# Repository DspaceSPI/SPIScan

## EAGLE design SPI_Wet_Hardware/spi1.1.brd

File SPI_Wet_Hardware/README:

All this is from Paul - paul@taniwha.com

Wet end SPI board and software:

spi1.1.sch		- rev 1.1 eagle files
spi1.1.brd

gerbers/...		- what I taped out with

avr162write.cmd 	- shell script to init the serial USB chip
arduino-16usb/ 		- code it was inited with

main.cmd 		- shell script to init the main cpu
stk500boot_v2_mega2560.hex - code to init it with

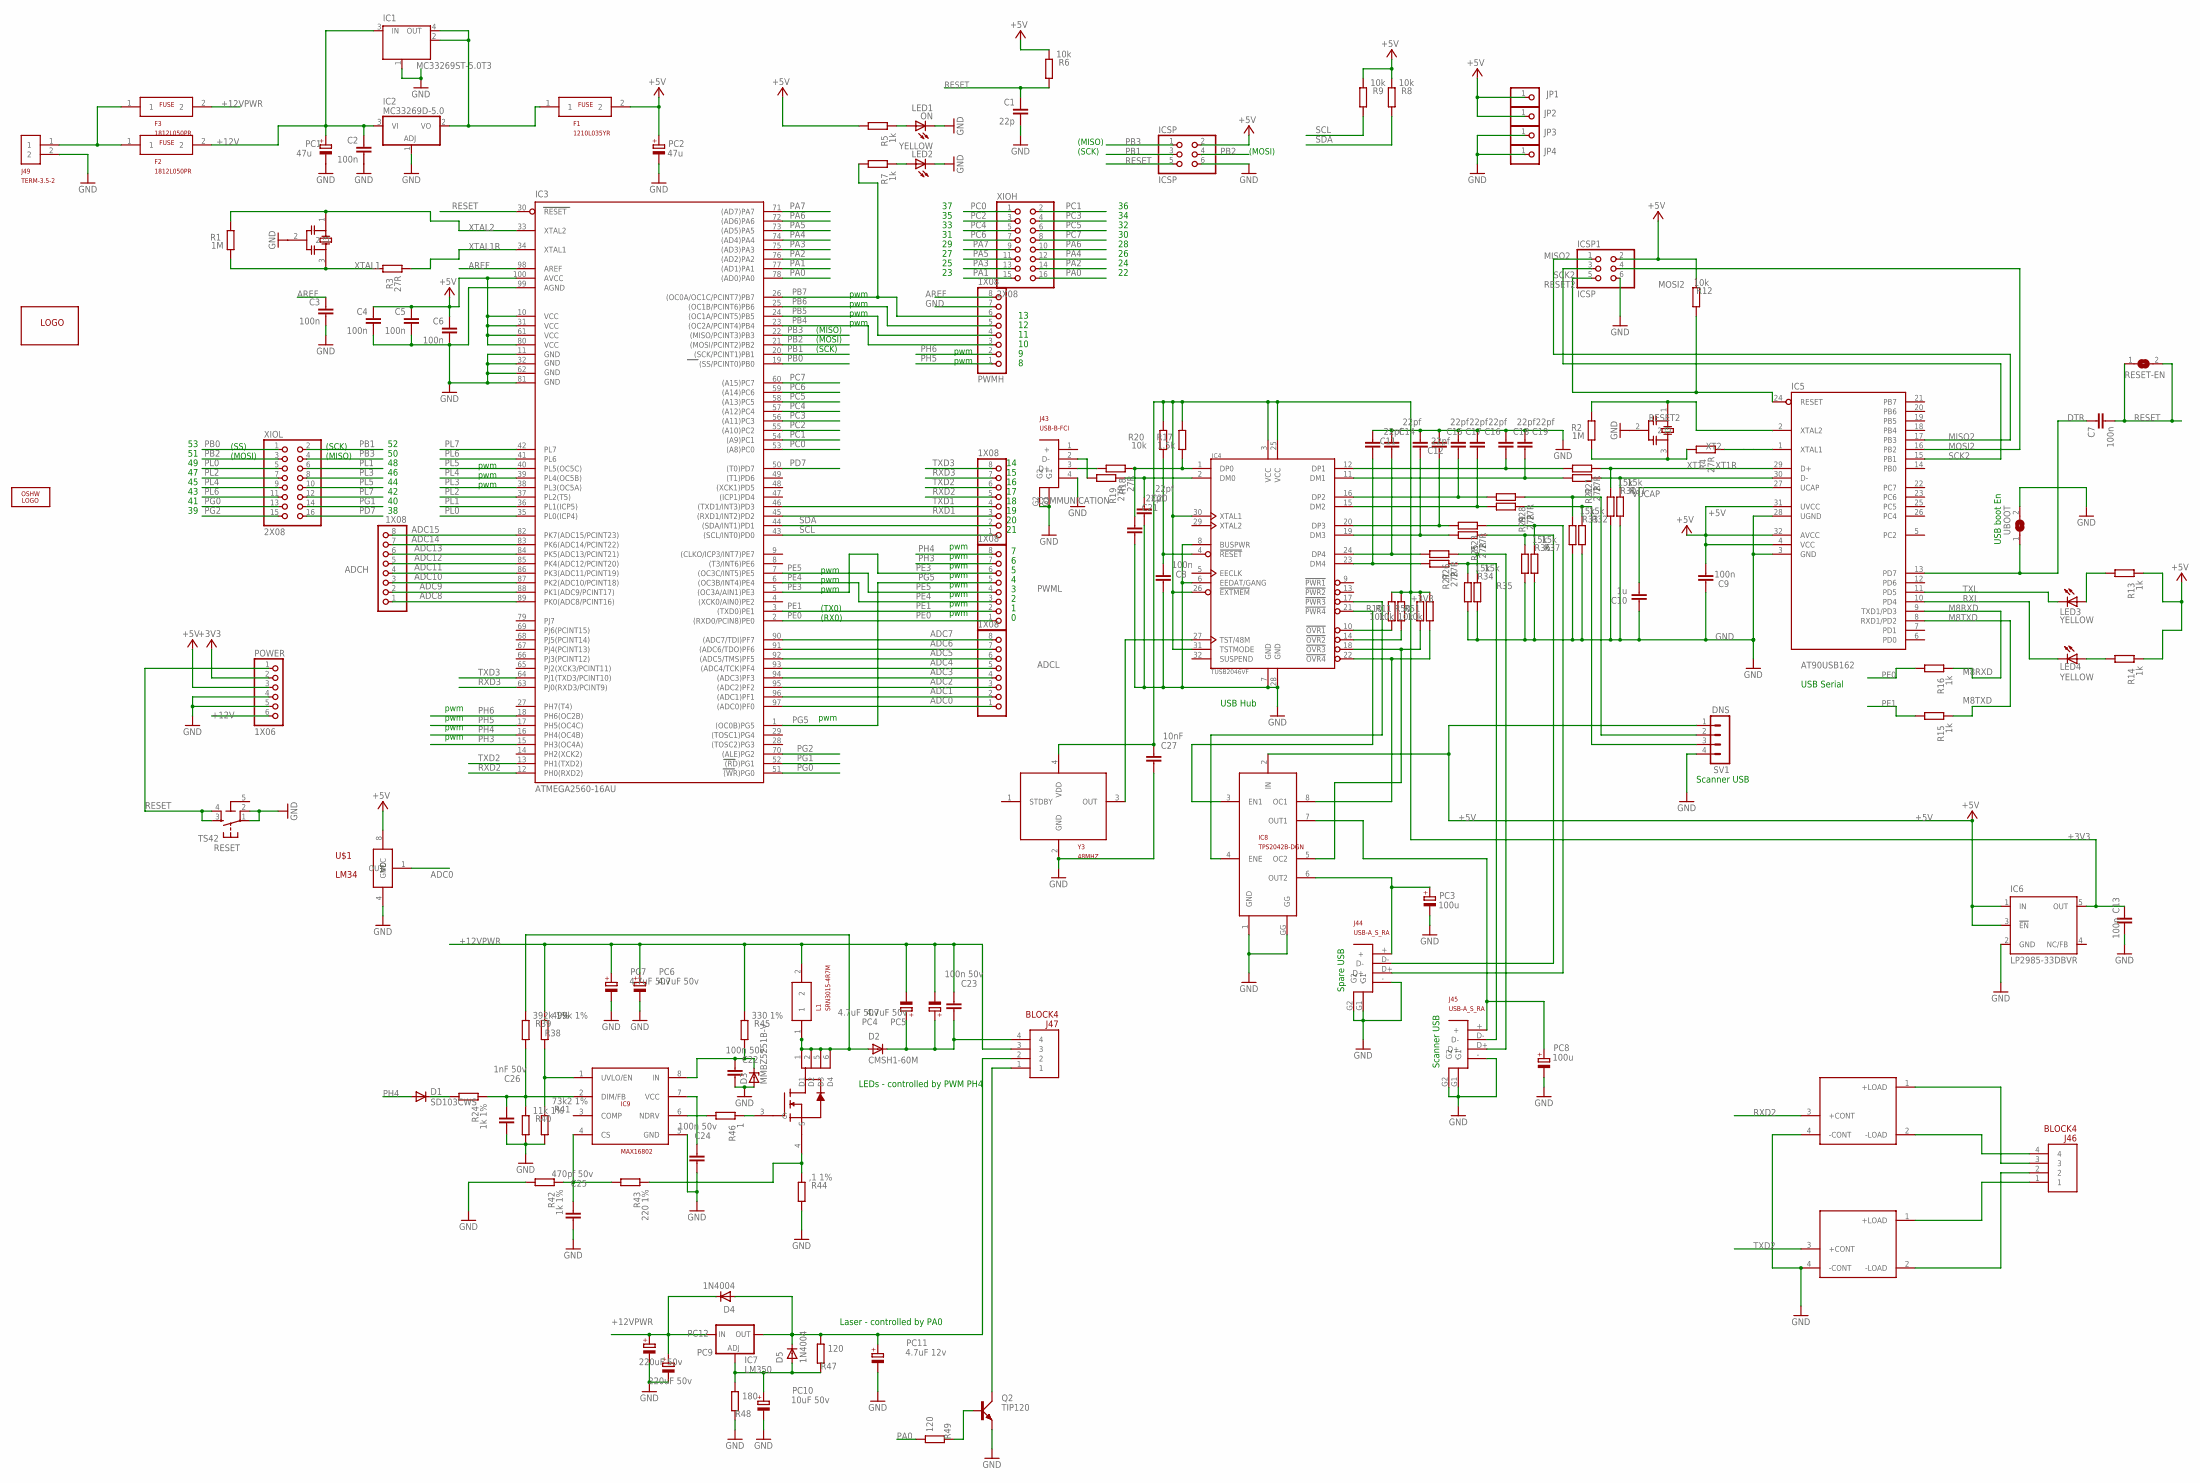
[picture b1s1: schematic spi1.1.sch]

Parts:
ADCH: 1X08
ADCL: 1X08
C1: 22p; C0603-ROUND
C2, C3, C4, C5, C6, C7, C8, C9, C13: 100n; C0603-ROUND
C10: 1u; C0603-ROUND
C11, C12, C14, C15, C16, C17, C18, C19, C20, C21: 22pf; C0603-ROUND
C22, C23, C24: 100n 50v; C0603-ROUND
C25: 470pf 50v; C0603-ROUND
C26: 1nF 50v; C0603-ROUND
C27: 10nF; C0603-ROUND
COMMUNICATION: 1X08
D1: SD103CWS; SOD323-W
D2: CMSH1-60M; SMA-DO214AC
D3: MMBZ5251B-V; SOT23
D4, D5: 1N4004; SMA-DO214AC
F1: 1210L035YR; POLY6
F2, F3: 1812L050PR; POLY15
IC1: MC33269ST-5.0T3; SOT223
IC2: MC33269D-5.0; DPACK
IC3: ATMEGA2560-16AU; TQFP100
IC4: TUSB2046VF; TQFP32-08
IC5: AT90USB162; TQFP32-08
IC6: LP2985-33DBVR; SOT23-DBV
IC7: LM350; 317TS
IC8: TPS2042B-DGN; DGN-8
IC9: MAX16802; USOP-8
ICSP, ICSP1: ICSP; 2X03
J43: USB-B-FCI; USB-B
J44, J45: USB-A_S_RA; USB-A
J46, J47: BLOCK4; TERM3.5-4
J49: TERM-3.5-2; TERM3.5-2
JP1, JP2, JP3, JP4: PINHD-1X1; 1X01
L1: SRN3015-4R7M; INDUCT1
LED2, LED3, LED4: YELLOW; CHIP-LED0805
LOGO2: OSHW_LOGO_FILLX0350-NT; OSHW_FILLX350_NOTEXT
ON: LED1; CHIP-LED0805
PC1, PC2: 47u; UD-6,3X7,7_NICHICON
PC3, PC8: 100u; UD-6,3X7,7_NICHICON
PC4, PC5, PC6, PC7: 4.7uF 50v; PANASONIC_C
PC9, PC12: 220uF 50v; PANASONIC_G
PC10: 10uF 50v; PANASONIC_D
PC11: 4.7uF 12v; PANASONIC_C
POWER: 1X06
PWMH: 1X08
PWML: 1X08
Q2: TIP120; TO220AV
R1, R2: 1M; R0603-ROUND
R3, R4, R18, R19, R21, R22, R23, R25, R26, R27, R28, R29: 27R; R0603-ROUND
R5, R7, R13, R14, R15, R16: 1k; R0603-ROUND
R6, R8, R9, R10, R11, R12, R20, R50, R51: 10k; R0603-ROUND
R17: 1.5k; R0603-ROUND
R24, R42: 1k 1%; R0603-ROUND
R30, R31, R32, R33, R34, R35, R36, R37: 15k; R0603-ROUND
R38: 499k 1%; R0603-ROUND
R39: 392k 1%; R0603-ROUND
R40: 11k 1%; R0603-ROUND
R41: 73k2 1%; R0603-ROUND
R43: 220 1%; R0603-ROUND
R44: ,1 1%; R1206
R45: 330 1%; R1206
R46: 1; R0603-ROUND
R47, R49: 120; R0603-ROUND
R48: 180; R0603-ROUND
RELAY1, RELAY2: XRELAY
RESET: TS42
RESET-EN: SJ
SV1: DNS; MA04-1
U$1: LM34; SS08
U$6: SI3458DVB; TSOP6
U$15: LOGO
UBOOT: SJ
XIOH: 2X08
XIOL: 2X08
Y1, Y2: AWSCR; RESONATOR1
Y3: 48MHZ; XTAL1

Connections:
5-GND: RESET.5 (5-GND)
+3V3: C13.2, C27.1, IC4.3 (VCC), IC4.25 (VCC), IC4.26 (!EXTMEM), IC4.30 (XTAL1), IC4.31 (TSTMODE), IC6.5 (OUT), POWER.2, R10.2, R11.2, R17.2, R20.2, R50.2, R51.2, Y3.4 (VDD)
+5V: C4.1, C5.1, C6.1, C9.1, F1.2, IC3.10 (VCC), IC3.31 (VCC1), IC3.61 (VCC2), IC3.80 (VCC3), IC3.100 (AVCC), IC5.4 (VCC), IC5.31 (UVCC), IC5.32 (AVCC), IC6.1 (IN), IC6.3 (!EN), IC8.2 (IN), ICSP.2, ICSP1.2, JP1.1, JP2.1, PC2.+, POWER.3, R5.2, R6.1, R8.1, R9.1, R12.1, R13.1, R14.1, SV1.1, U$1.8 (VCC)
+12V: C2.1, F2.2, IC1.3 (IN), IC2.3 (VI), PC1.+, POWER.6
+12VPWR: C23.1, D4.K (C), F3.2, IC7.3 (IN), J47.3, L1.2, PC4.-, PC5.-, PC6.+, PC7.+, PC9.+, PC12.+, R38.1, R45.1
ADC0: ADCL.1, IC3.97 ((ADC0)PF0), U$1.1 (OUT)
ADC1: ADCL.2, IC3.96 ((ADC1)PF1)
ADC2: ADCL.3, IC3.95 ((ADC2)PF2)
ADC3: ADCL.4, IC3.94 ((ADC3)PF3)
ADC4: ADCL.5, IC3.93 ((ADC4/TCK)PF4)
ADC5: ADCL.6, IC3.92 ((ADC5/TMS)PF5)
ADC6: ADCL.7, IC3.91 ((ADC6/TDO)PF6)
ADC7: ADCL.8, IC3.90 ((ADC7/TDI)PF7)
ADC8: ADCH.1, IC3.89 (PK0(ADC8/PCINT16))
ADC9: ADCH.2, IC3.88 (PK1(ADC9/PCINT17))
ADC10: ADCH.3, IC3.87 (PK2(ADC10/PCINT18))
ADC11: ADCH.4, IC3.86 (PK3(ADC11/PCINT19))
ADC12: ADCH.5, IC3.85 (PK4(ADC12/PCINT20))
ADC13: ADCH.6, IC3.84 (PK5(ADC13/PCINT21))
ADC14: ADCH.7, IC3.83 (PK6(ADC14/PCINT22))
ADC15: ADCH.8, IC3.82 (PK7(ADC15/PCINT23))
AREF: C3.1, IC3.98 (AREF), PWMH.8
DTR: C7.1, IC5.13 (PD7), UBOOT.1
GND: C1.2, C2.2, C3.2, C4.2, C5.2, C6.2, C8.2, C9.2, C10.2, C11.1, C12.1, C13.1, C14.1, C15.1, C16.1, C17.1, C18.1, C19.1, C20.2, C21.2, C22.2, C24.2, C25.2, C26.2, C27.2, D3.1 (A), IC1.1 (GND/ADJ), IC2.1 (ADJ), IC3.11 (GND), IC3.32 (GND1), IC3.62 (GND2), IC3.81 (GND3), IC3.99 (AGND), IC4.6 (EEDAT/GANG), IC4.7 (GND), IC4.8 (BUSPWR), IC4.28 (GND), IC5.3 (GND), IC5.28 (UGND), IC6.2 (GND), IC8.1 (GND), IC8.GG, IC9.5 (GND), ICSP.6, ICSP1.6, J43.4 (-), J43.G1, J43.G2, J44.-, J44.G1, J44.G2, J45.-, J45.G1, J45.G2, J49.2, JP3.1, JP4.1, LED2.C, ON.C, PC1.-, PC2.-, PC3.-, PC6.-, PC7.-, PC8.-, PC9.-, PC10.-, PC11.-, PC12.-, POWER.4, POWER.5, PWMH.7, Q2.E, R30.2, R31.2, R32.2, R33.2, R34.2, R35.2, R36.2, R37.2, R40.2, R41.2, R42.2, R44.2, R48.2, RELAY1.4 (-CONT), RELAY2.4 (-CONT), RESET.1, RESET.2, SV1.4, U$1.4 (GND), UBOOT.2, Y1.2, Y2.2, Y3.2 (GND)
M8RXD: IC5.9 (TXD1/PD3), R16.1
M8TXD: IC5.8 (RXD1/PD2), R15.1
MISO2: IC5.17 (PB3), ICSP1.1
MOSI2: IC5.16 (PB2), ICSP1.4
unnamed: J44.D+, R23.1, R37.1
unnamed: LED2.A, R7.1
unnamed: ON.A, R5.1
unnamed: R28.1, R33.1, SV1.2
unnamed: R29.1, R32.1, SV1.3
unnamed: IC4.10 (!OVR1), R10.1
unnamed: IC4.14 (!OVR2), R11.1
unnamed: IC4.17 (!PWR3), IC8.4 (ENE)
unnamed: C21.1, IC4.1 (DP0), R17.1, R18.1
unnamed: J45.D+, R26.1, R35.1
unnamed: C8.1, IC4.4 (!RESET), R20.1
unnamed: IC4.21 (!PWR4), IC8.3 (EN1)
unnamed: IC4.18 (!OVR3), IC8.5 (OC2), R50.1
unnamed: IC4.22 (!OVR4), IC8.8 (OC1), R51.1
unnamed: IC8.6 (OUT2), J44.+, PC3.+
unnamed: IC8.7 (OUT1), J45.+, PC8.+
unnamed: C15.2, IC4.20 (DP3), R23.2
unnamed: C17.2, IC4.16 (DP2), R28.2
unnamed: C16.2, IC4.15 (DM2), R29.2
unnamed: C12.2, IC4.19 (DM3), R25.2
unnamed: C14.2, IC4.24 (DP4), R26.2
unnamed: C11.2, IC4.23 (DM4), R27.2
unnamed: C18.2, IC4.12 (DP1), R21.2
unnamed: C19.2, IC4.11 (DM1), R22.2
unnamed: IC5.30 (D-), R22.1, R31.1
unnamed: IC5.29 (D+), R21.1, R30.1
unnamed: C20.1, IC4.2 (DM0), R19.1
unnamed: J44.D-, R25.1, R36.1
unnamed: D1.C, R24.2
unnamed: C26.1, IC9.2 (DIM/FB), R24.1, R39.2, R40.1
unnamed: J45.D-, R27.1, R34.1
unnamed: IC9.1 (UVLO/EN), R38.2, R41.1
unnamed: C23.2, D2.K (C), J47.4, PC4.+, PC5.+
unnamed: IC4.27 (TST/48M), Y3.3 (OUT)
unnamed: D2.A, L1.1, R39.1, U$6.1 (D1), U$6.2 (D2), U$6.5 (D3), U$6.6 (D4)
unnamed: C24.1, IC9.7 (VCC)
unnamed: F1.1, IC1.2 (OUT), IC1.4 (OUT), IC2.2 (VO)
unnamed: C25.1, IC9.4 (CS), R42.1, R43.2
unnamed: D5.A, IC7.1 (ADJ), PC10.+, R47.2, R48.1
unnamed: C22.1, D3.3 (C), IC9.8 (IN), R45.2
unnamed: R43.1, R44.1, U$6.4 (S)
unnamed: F2.1, F3.1, J49.1
unnamed: IC9.6 (NDRV), R46.2
unnamed: R46.1, U$6.3 (G)
unnamed: J43.2 (D-), R19.2
unnamed: J43.3 (D+), R18.2
unnamed: D4.A, D5.K (C), IC7.2 (OUT), J47.2, PC11.+, R47.1
unnamed: J47.1, Q2.C
unnamed: J46.4, RELAY1.2 (-LOAD)
unnamed: J46.1, RELAY2.1 (+LOAD)
unnamed: J46.3, RELAY1.1 (+LOAD)
unnamed: Q2.B, R49.2
unnamed: J46.2, RELAY2.2 (-LOAD)
unnamed: LED4.A, R14.2
unnamed: LED3.A, R13.2
PA0: IC3.78 ((AD0)PA0), R49.1, XIOH.16
PA1: IC3.77 ((AD1)PA1), XIOH.15
PA2: IC3.76 ((AD2)PA2), XIOH.14
PA3: IC3.75 ((AD3)PA3), XIOH.13
PA4: IC3.74 ((AD4)PA4), XIOH.12
PA5: IC3.73 ((AD5)PA5), XIOH.11
PA6: IC3.72 ((AD6)PA6), XIOH.10
PA7: IC3.71 ((AD7)PA7), XIOH.9
PB0: IC3.19 ((SS/PCINT0)PB0), XIOL.1
PB1: IC3.20 ((SCK/PCINT1)PB1), ICSP.3, XIOL.2
PB2: IC3.21 ((MOSI/PCINT2)PB2), ICSP.4, XIOL.3
PB3: IC3.22 ((MISO/PCINT3)PB3), ICSP.1, XIOL.4
PB4: IC3.23 ((OC2A/PCINT4)PB4), PWMH.3
PB5: IC3.24 ((OC1A/PCINT5)PB5), PWMH.4
PB6: IC3.25 ((OC1B/PCINT6)PB6), PWMH.5
PB7: IC3.26 ((OC0A/OC1C/PCINT7)PB7), PWMH.6, R7.2
PC0: IC3.53 ((A8)PC0), XIOH.1
PC1: IC3.54 ((A9)PC1), XIOH.2
PC2: IC3.55 ((A10)PC2), XIOH.3
PC3: IC3.56 ((A11)PC3), XIOH.4
PC4: IC3.57 ((A12)PC4), XIOH.5
PC5: IC3.58 ((A13)PC5), XIOH.6
PC6: IC3.59 ((A14)PC6), XIOH.7
PC7: IC3.60 ((A15)PC7), XIOH.8
PD7: IC3.50 ((T0)PD7), XIOL.16
PE0: IC3.2 ((RXD0/PCIN8)PE0), PWML.1, R16.2
PE1: IC3.3 ((TXD0)PE1), PWML.2, R15.2
PE3: IC3.5 ((OC3A/AIN1)PE3), PWML.6
PE4: IC3.6 ((OC3B/INT4)PE4), PWML.3
PE5: IC3.7 ((OC3C/INT5)PE5), PWML.4
PG0: IC3.51 ((WR)PG0), XIOL.13
PG1: IC3.52 ((RD)PG1), XIOL.14
PG2: IC3.70 ((ALE)PG2), XIOL.15
PG5: IC3.1 ((OC0B)PG5), PWML.5
PH3: IC3.15 (PH3(OC4A)), PWML.7
PH4: D1.A, IC3.16 (PH4(OC4B)), PWML.8
PH5: IC3.17 (PH5(OC4C)), PWMH.1
PH6: IC3.18 (PH6(OC2B)), PWMH.2
PL0: IC3.35 (PL0(ICP4)), XIOL.5
PL1: IC3.36 (PL1(ICP5)), XIOL.6
PL2: IC3.37 (PL2(T5)), XIOL.7
PL3: IC3.38 (PL3(OC5A)), XIOL.8
PL4: IC3.39 (PL4(OC5B)), XIOL.9
PL5: IC3.40 (PL5(OC5C)), XIOL.10
PL6: IC3.41 (PL6), XIOL.11
PL7: IC3.42 (PL7), XIOL.12
RESET: C1.1, C7.2, IC3.30 (RESET), ICSP.5, POWER.1, R6.2, RESET.3, RESET.4, RESET-EN.1, RESET-EN.2
RESET2: IC5.24 (RESET), ICSP1.5, R12.2
RXD1: COMMUNICATION.3, IC3.45 ((RXD1/INT2)PD2)
RXD2: COMMUNICATION.5, IC3.12 (PH0(RXD2)), RELAY1.3 (+CONT)
RXD3: COMMUNICATION.7, IC3.63 (PJ0(RXD3/PCINT9))
RXL: IC5.10 (PD4), LED4.C
SCK2: IC5.15 (PB1), ICSP1.3
SCL: COMMUNICATION.1, IC3.43 ((SCL/INT0)PD0), R9.2
SDA: COMMUNICATION.2, IC3.44 ((SDA/INT1)PD1), R8.2
TXD1: COMMUNICATION.4, IC3.46 ((TXD1/INT3)PD3)
TXD2: COMMUNICATION.6, IC3.13 (PH1(TXD2)), RELAY2.3 (+CONT)
TXD3: COMMUNICATION.8, IC3.64 (PJ1(TXD3/PCINT10))
TXL: IC5.11 (PD5), LED3.C
VUCAP: C10.1, IC5.27 (UCAP)
XT1: R2.1, R4.2, Y2.3
XT1R: IC5.1 (XTAL1), R4.1
XT2: IC5.2 (XTAL2), R2.2, Y2.1
XTAL1: R1.1, R3.2, Y1.3
XTAL1R: IC3.34 (XTAL1), R3.1
XTAL2: IC3.33 (XTAL2), R1.2, Y1.1

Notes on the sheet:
(SCK)
(MISO)
(MOSI)
pwm
(TX0)
(RX0)
(SS)
USB boot En
Scanner USB
USB Serial
USB Hub
Spare USB
Laser - controlled by PA0
LEDs - controlled by PWM PH4

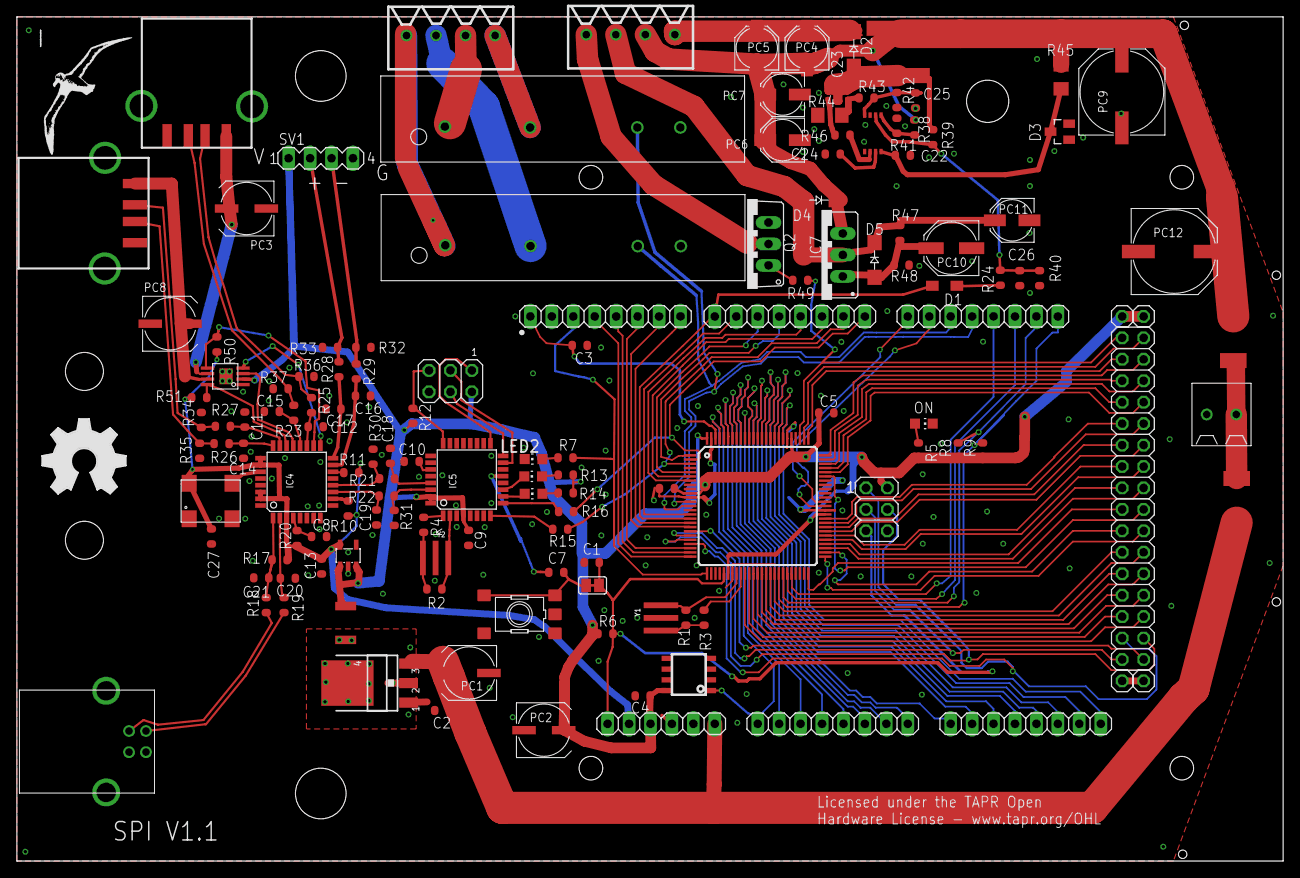
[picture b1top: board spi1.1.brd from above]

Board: 2 copper layers, 150.0 x 100.0 mm, 146 parts (1 on the bottom side), 148 nets.

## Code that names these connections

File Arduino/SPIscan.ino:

/*
Process serial commands from the host and send responses
Serial packet protocol is:
 <sync>       Byte, always 0xAA
 <command>    Byte
 <transID>    Byte
 <paramLen>   Byte
 <parameters> Byte array, paramLen bytes (could be 0)
 <checksum>   Byte, low byte of sum of <sync>..<last parameter>
 
<transID> is sent by the host and used in any response(s) and can be any value
except 00, which is reserved for messages sent by the Arduino without being asked.

The Arduino is predefined as driving:
 - two pump relays on RXD2 and TXD2
 - a PWM LED drive PH4
 - a laser enable PA0
 - a temp sensor on PC7 (A15)
 
*/

#include "SPIproto.h"      // Serial protocol constants

// Configurable parameters
enum {
  kBaudRate = 115200,
  kMaxMsgSize = 50,      // Max data size
  
  kTotalSize = kHdrSize + kMaxMsgSize + kCksumSize,
};

// Less configurable parameters
const char kSysInfoStr[] = "SPIScan " __DATE__ __TIME__ ;

//====================== Predefined pins  ======================

enum {
  kOnboardLEDPin = 13,
  kPump1Pin = 16,
  kPump2Pin = 17
  
};

struct KnownPin {
  byte pinNum;
  bool outDir;
  bool outState;
};

const KnownPin gPredefinedPins[] = {
  { kOnboardLEDPin, OUTPUT, LOW },    // Onboard LED
  { kPump1Pin, OUTPUT, LOW },    // PH0(RXD2) pump drive
  { kPump2Pin, OUTPUT, LOW },    // PH1(TXD2) pump drive
  { 7,  OUTPUT, LOW },    // PH4 LED drive (PWM)
  { 22, OUTPUT, LOW }     // PA0 laser enable
};

enum { kNPredefs = sizeof(gPredefinedPins)/sizeof(KnownPin) };

//======================= Globals ========================
byte   gInMsg[kTotalSize];
byte   gCkSum = 0;
Sp_Error   gNetErr = kNoErr;      // Last error 
long   gNetParam;    // Last error parameter
short  gInWrIdx = 0;

// ----------------------- Packet protocol --------------------------

void SendMsg(Sp_Command cmd, byte transID, const void* p, byte len)
{
  int i;
  byte header[kHdrSize] = { kSyncByte, cmd, transID, len };
  byte cksum = kSyncByte + cmd + transID + len;
  
  Serial.write(&header[0],kHdrSize);
  if (len>0) {
     const byte* bp = (byte*)p;
     for (i=0; i<len; i++)
        cksum += bp[i];
     Serial.write(bp,len);
  }
  Serial.write(cksum);
}

void SendErrMsg(Sp_Error errcode, byte transID, long parameter)
{
  uint8_t msg[5] = { errcode, parameter>>24, parameter>>16, parameter>>8, parameter & 0xFF };
  SendMsg(kCCError, transID, &msg, sizeof(msg));
}

void SendMsgOrNetErr(Sp_Command resp, byte transID, void* dataP, byte nBytes)
// Either send specified message or an error code if gNetErr is nonzero: useful
// for responding to list messages
{
  if (gNetErr==kNoErr)
    SendMsg(resp,transID,dataP,nBytes);
  else
    SendErrMsg(gNetErr,transID,gNetParam);
}

bool GetMsg()
// Call whenever convenient, will return true if a valid and complete message is in the gInMsg buffer
// If it returns true you *must* process the message before calling again
{
   int i,n;
   byte b;
   
   n = Serial.available();
   
   for (i=0; i<n; i++) {
     b = Serial.read();
     //Serial.write(b);
     if (gInWrIdx==0) {
       if (b==kSyncByte) {
         gInMsg[gInWrIdx++] = b;
         gCkSum = b;
       }
     } else {
        if (gInWrIdx < kTotalSize)
          gInMsg[gInWrIdx++] = b;
        if (gInWrIdx > kLenPos && gInWrIdx >= kHdrSize + gInMsg[kLenPos] + kCksumSize) {
            // Message complete; reset wridx
            gInWrIdx = 0;
            if (gCkSum != b) {
               return false;      // Ignore if it has a bad checksum
            } else if (gInMsg[kLenPos]>kMaxMsgSize) {
                SendErrMsg(kErrMsgOversize,gInMsg[kIDPos],gInMsg[kLenPos]);    // valid, but too big for buffer
                return false;
            } else
                return true; 
        } else
           gCkSum += b;
     }
   } // for
   return false;
}

//------------------------ Utilities ---------------------------------------

bool isInput(byte pinNum)
{
  volatile byte* rp = portModeRegister(digitalPinToPort(pinNum));
  return (*rp & digitalPinToBitMask(pinNum)) == 0;
}

bool isPredefined(byte aPin)
{
  int i;
  for (i=0 ; i<kNPredefs; i++) 
     if (gPredefinedPins[i].pinNum==aPin)
       return true;
  return false;
}

//------------------------ Core commands ----------------------------------

void SetMode(byte pinNum, byte value)
{
   // Check its a valid pin number and it doesn't have a predefined direction
   if (digitalPinToPort(pinNum)==NOT_A_PIN) {
      gNetErr = kErrInvalidPin;
      gNetParam = pinNum;
   } else if (isPredefined(pinNum)) {
      gNetErr = kErrPredefined;
      gNetParam = pinNum;
   } else
      pinMode(pinNum,value);
}

void SetPin(byte pinNum, byte value)
{
   // Check its a valid pin number and it isn't an input
   if (digitalPinToPort(pinNum)==NOT_A_PIN) {
      gNetErr = kErrInvalidPin;
      gNetParam = pinNum;
   } else if (isInput(pinNum)) {
      gNetErr = kErrOutToInput;
      gNetParam = pinNum;
   } else
      digitalWrite(pinNum,value);
}

byte GetPin(byte pinNum)
{
  // Check its a valid pin number. Its OK to read back from outputs
  if (digitalPinToPort(pinNum)==NOT_A_PIN) {
      gNetErr = kErrInvalidPin;
      gNetParam = pinNum;
      return LOW;
  } else 
      return digitalRead(pinNum);
}

void AnalogReadPinList(byte transID, byte* pinNums, byte nPins)
{
  int i;
  int gValues[kMaxMsgSize/sizeof(int)];
  
  for (i=0; i<nPins; i++)
    // Check for valid analog pin
    if (pinNums[i] > NUM_ANALOG_INPUTS) {
      gNetErr = kErrInvalidPin;
      gNetParam = pinNums[i];
    } else { 
      gValues[i] = analogRead(pinNums[i]);
    }
      
  SendMsgOrNetErr(kCCPinValues, transID, gValues, nPins);
}

void GetPinList(byte transID, byte* pinNums, byte nPins)
{
  int i;
  byte gValues[kMaxMsgSize];
  
  for (i=0; i<nPins; i++)
    gValues[i] = GetPin(pinNums[i]);
  SendMsgOrNetErr(kCCPinStates, transID, gValues, nPins);
}

void SetPinList(byte transID, byte* pinNums, byte nPins)
{
  int i;
  
  for (i=0; i<nPins; i++)
    SetPin(pinNums[i] & 0x7F, (pinNums[i] & 0x80) ? HIGH : LOW);
  SendMsgOrNetErr(kCCNoErr, transID, NULL, 0);
}

void SetModeList(byte transID, byte* pinNums, byte nPins)
{
  int i;
  
  for (i=0; i<nPins; i++)
    SetMode(pinNums[i] & 0x7F, (pinNums[i] & 0x80) ? OUTPUT : INPUT);
  SendMsgOrNetErr(kCCNoErr, transID, NULL, 0);
}

void AnalogWriteList(byte transID, byte* pvList, byte nValues)
{
  int i;
  byte pinNum;
  
  for (i=0; i<nValues; i++) {
    pinNum = pvList[0];
    if (isInput(pinNum)) {
      gNetErr = kErrOutToInput;
      gNetParam = pinNum;
    } else 
      analogWrite(pinNum, pvList[1]);
    pvList += 2;
  }
  SendMsgOrNetErr(kCCNoErr, transID, NULL, 0);
}

void ProcessMsg()
{
  gNetErr = kNoErr;
  switch (gInMsg[kCmdPos]) {
    
    case kCCGetPins:
      GetPinList(gInMsg[kIDPos], &gInMsg[kDataPos], gInMsg[kLenPos]);
      break;
      
    case kCCSetPins:
      SetPinList(gInMsg[kIDPos], &gInMsg[kDataPos], gInMsg[kLenPos]);
      break;
      
    case kCCSetPinModes:
      SetModeList(gInMsg[kIDPos], &gInMsg[kDataPos], gInMsg[kLenPos]);
      break;
    
    case kCCAnalogReads:
      AnalogReadPinList(gInMsg[kIDPos], &gInMsg[kDataPos], gInMsg[kLenPos]);
      break;
    
    case kCCSetPWM:
      if (gInMsg[kLenPos] & 1)    // Must be a list of pin/value pairs
        SendErrMsg(kErrOddPWM,gInMsg[kIDPos],gInMsg[kLenPos]);
      else
        AnalogWriteList(gInMsg[kIDPos], &gInMsg[kDataPos], gInMsg[kLenPos]/2);
      break;
    
    case kCCGetSysInfo: {
         SendMsg(kCCSysInfo,gInMsg[kIDPos],kSysInfoStr,strlen(kSysInfoStr));
      } break;
    
    default:
      SendErrMsg(kErrUnknownCmd, gInMsg[kIDPos], gInMsg[kCmdPos]);
      break;
  }
}


//---------------------------- Arduino main ------------------------

void setup()
{
   int i;
   
   // Setup predefined state
   for (i=0 ; i<kNPredefs; i++) {
     pinMode(gPredefinedPins[i].pinNum, gPredefinedPins[i].outDir);
     digitalWrite(gPredefinedPins[i].pinNum, gPredefinedPins[i].outState);
   }
   // Turn on serial port
   gInWrIdx = 0;
   Serial.begin(kBaudRate);
  
   SendMsg(kCCSysInfo,0,kSysInfoStr,strlen(kSysInfoStr));
}

long count = 0;

void loop()
{
   while (GetMsg())
     ProcessMsg();
}

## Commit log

2012-04-24 first drafts
2012-04-27 Added LiDE700F USB packet log for restart, preview, colour scan, and greyscale scan
2012-04-27 Added SANE Man Pages
2012-04-30 Added base structure for boat box electronics
2012-05-12 Seperate out protocol header, add typedefs for errors and command constants
2012-05-21 Added first DRAFT of SANE backend for Lide700f for intial test purposes
2012-06-09 Fix minor bugs, add demo host interface files in C/POSIX
2012-07-12 added wet end design and code
2012-07-12 remove .o files
2012-08-13 add file for Brian
2012-08-20 Add ability to initialise PWM outputs for LED at startup
2012-08-21 Added scanner control code (needs sane libraries to be installed) Added code to build python bindings for scanning and for Michael's Arduino RPC interface glue
2012-08-22 - added GPS code - changed arduino code to possibly handle usb being unplugged (untested) - created unified startup_dspace() that starts all these subsystems (should be called first by python)
2012-08-22 - push actual changes - gps changes - unified startup routines - try to add USB retry code to arduino code
2012-08-22 add gps accessor functions
2012-08-28 GUI directory obsolete. MockSPIGUI added which is a complete Pyramid scaffold for serving out GUI.
2012-08-29 - working tiff output - USB retry works when cable unplugged
2012-09-06 - new API for scan start polling for finish - support for setting system time from GPS time
2013-02-13 Added pyramid based gui files
    contains basic templates, interface structure
2013-02-14 CSS changes added full bootstrap
    Added twitter bootstrap files, mjpg-streamer files and corrected CSS
2013-02-16 modified GUI, included jquery and other javascripts, prior to JSON
2013-03-01 Added SANE files known to work instead of Ubuntu repositories
2013-03-04 modifications to pyramid to allow postgresql db access, sample gis data
2013-03-05 Corrected some time stamp data types into database and gui timeclock js
2013-03-05 basic inelegant capture camera frame working
2013-03-06 added db columns and datatypes added frame grab labelling watermarking faulty
2013-03-07 fixed scan source fixed watermarking of cam captures
2013-03-10 modified add view config to dynamically serve lastscan.jpg from /home/brian/scan
2013-03-13 Added documentation to scan.c and now working repeatedly, passing dictionary (tuples) from db query to spifiles page
2013-03-16 Vastly firmed up the schema and removed psycopg for all sqlalchemy operations and added templates for CAM SPI and LOG
2013-03-30 Oneway settings setup persistance through filesystem is working
2013-03-30 minor error fix from last
2013-03-30 fixed errors in last record javascript

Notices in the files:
SPI_Wet_Hardware/spi1.1.brd:
Copyright 2012 Paul Campbell -
Licensed under the TAPR Open
Hardware License - www.tapr.org/OHL
